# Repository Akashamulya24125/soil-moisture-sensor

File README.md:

\# Soil Moisture Sensor — V1

\### Custom PCB Design · Capacitive Sensing · KiCad · Circuit Simulation

A custom soil-moisture sensing hardware project focused on PCB-level capacitive sensing, analog signal conditioning, circuit simulation, and hardware-to-software interface design.

This repository preserves the \*\*Soil Sensor V1 KiCad design\*\*, supporting design documentation, electrical-rule reports, and PCB fabrication outputs.

\---

\## 1. Project Overview

The objective is to develop a custom soil moisture sensor in which the sensing electrodes are formed directly by copper patterns on the PCB rather than using a separate commercial sensor breakout module.

The probe uses two interlocking copper comb electrodes separated by a small gap. Changes in the surrounding soil environment affect the effective capacitance of the sensing structure. The analog front end converts the resulting electrical response into an output voltage that can be measured by a microcontroller.

The project also defines an interface for reading sensor measurements through an Arduino Uno and displaying moisture readings on a laptop.

\*\*Primary engineering goals\*\*

\- Design the sensor circuitry and PCB using KiCad.

\- Implement a PCB-integrated capacitive sensing structure.

\- Simulate the oscillator and analog signal-conditioning stages.

\- Define a consistent electrical and serial communication interface.

\- Generate fabrication data and document the design for further testing.

\## 2. System Architecture

The documented system follows this signal path:

```text

Soil / Probe Environment

&#x20;         |

&#x20;         v

PCB Capacitive Comb Electrodes

&#x20;         |

&#x20;         v

555-Timer Oscillator

&#x20;         |

&#x20;         v

Sensing Network

&#x20;         |

&#x20;         v

Diode Rectifier + RC Filter

&#x20;         |

&#x20;         v

Analog Output (AOUT)

&#x20;         |

&#x20;         v

Arduino Uno — Analog Input A0

&#x20;         |

&#x20;         v

USB Serial Communication

&#x20;         |

&#x20;         v

Laptop Moisture Monitor Application

```

The custom sensor PCB provides the electrical signal. The Arduino reads the analog output, and the documented serial interface allows the laptop application to display the moisture percentage and raw ADC reading.

This describes the intended system architecture; physical end-to-end validation is still required.

\## 3. Hardware Design

\### PCB-integrated capacitive probe

The sensing element is formed by copper comb patterns in the PCB layout. The electrodes are not separate purchased components.

The soil occupies the electric-field region around and between the fingers. Changes in effective capacitance influence the analog sensing circuit.

Important design considerations include:

\- Electrode geometry and spacing.

\- Protection of the sensing structure from corrosion and unwanted exposure.

\- Separation of the sensing region from the electronics section.

\- Repeatable probe placement during calibration and testing.

\### Analog signal-conditioning circuit

The supplied schematic and circuit-design notes describe a 555-timer oscillator followed by a capacitive sensing network and a diode-based peak detector.

The circuit stages are:

1\. \*\*Oscillator:\*\* Generates the periodic excitation signal.

2\. \*\*Sensing network:\*\* Couples the probe's effective capacitance into the circuit response.

3\. \*\*Rectifier:\*\* Uses a small-signal diode to produce charging pulses.

4\. \*\*Filter and bleed network:\*\* Smooths the rectified signal into an analog output.

5\. \*\*Output interface:\*\* Provides VCC, GND, and AOUT connections.

The exact component packages and values should be checked against the current KiCad project and its committed BOM/footprint revision document.

\## 4. Electrical Interface

The accompanying Interface Control Document defines the intended Arduino-facing interface.

| Signal | Function |

|---|---|

| VCC | Sensor power input |

| GND | Common electrical reference |

| AOUT | Analog sensor output to Arduino A0 |

The documented prototype uses the Arduino Uno's 5 V supply and a common ground. The Arduino's 10-bit ADC produces raw readings in the range 0–1023.

The interface document gives an approximate AOUT expectation of \*\*1.5 V in wet conditions to 3.0 V in dry conditions\*\*. These are design expectations, not confirmed physical measurements.

\## 5. Circuit Simulation and Verification

The supplied simulation report documents electrical-only verification using \*\*KiCad 10 and ngspice\*\*.

\### Simulation configuration

| Parameter | Simulated setting |

|---|---|

| Supply voltage | 5 V DC |

| R1 | 1 kΩ |

| R2 | 10 kΩ |

| C1 | 1 nF |

| R3 | 10 kΩ |

| R4 | 100 kΩ |

| C3 | 10 nF |

| C4 | 100 nF |

| Probe representation | Ideal behavioral capacitance, C5 |

| Capacitance sweep | 100 pF–2.5 nF |

| Transient simulation end time | 50 ms |

\### Observed simulation results

The report records the following simulated behavior:

\- The 555 oscillator produced a repeating waveform at approximately 68.5 kHz.

\- The timing node exhibited the expected charge/discharge behavior.

\- Changes in the modeled sensing capacitance affected the Node-X waveform.

\- The diode exhibited repeated conduction events.

\- The RC network produced a smoother DC output at AOUT.

\- Increasing the modeled capacitance from 100 pF to 2.5 nF reduced the settled simulated AOUT voltage from approximately 2.90 V to 1.52 V.

These results demonstrate the expected behavior of the modeled signal chain under the tested simulation conditions.

\*\*Important distinction:\*\* C5 was an ideal simulated capacitor used to represent the sensing structure. It was not a measured capacitance of the physical PCB probe.

The simulated results therefore do not establish final moisture accuracy, real-soil performance, or the physical probe's dry/wet calibration.

\## 6. Arduino and Laptop Interface

The supplied firmware and application specifications define a wired monitoring architecture.

\### Arduino firmware interface

The firmware specification defines:

\- Analog input: Arduino A0.

\- ADC range: 0–1023.

\- Serial baud rate: 9600.

\- Update interval: 1000 ms, or one reading per second.

\- Output format:

```text

MOISTURE,<percent>,<raw>

```

Example:

```text

MOISTURE,62,743

```

The percentage is constrained to 0–100, while the raw field represents the direct ADC reading.

\### Laptop monitor application

The documented Python GUI is designed to:

\- Discover available serial/COM ports.

\- Connect to the Arduino.

\- Display the latest moisture percentage and raw ADC value.

\- Read serial data in a background thread so the GUI remains responsive.

\- Ignore malformed input lines.

\- Display a no-data status when valid readings have not arrived for more than three seconds.

The companion documents specify this integration contract. Executable firmware and laptop application source files are not included in the current tracked repository snapshot.

\## 7. Calibration and Physical Validation

Calibration values must be measured on the assembled sensor rather than inferred from simulation.

The supplied firmware document lists `DRY\_RAW = 750` and `WET\_RAW = 300` as \*\*placeholders\*\*. They must be replaced with actual measured values before final calibration.

The documented validation sequence is:

1\. Inspect the fabricated PCB and check continuity.

2\. Verify the supply and ground connections before connecting AOUT to the Arduino.

3\. Measure the output with the probe in open air under a controlled dry condition.

4\. Measure the output in the defined wet reference condition.

5\. Record the corresponding raw ADC readings.

6\. Update the firmware calibration constants using those measurements.

7\. Test the complete sensor → Arduino → USB serial → laptop application path.

8\. Evaluate repeatability under controlled soil conditions.

The supplied simulation report explicitly leaves physical probe validation and final dry/wet calibration pending.

\## 8. Repository Contents

The V1 repository contains the following project artifacts:

| File or directory | Purpose |

|---|---|

| `Soil\_Sensor\_v1.kicad\_pro` | KiCad project configuration |

| `Soil\_Sensor\_v1.kicad\_sch` | Circuit schematic |

| `Soil\_Sensor\_v1.kicad\_pcb` | PCB layout |

| `Soil\_Sensor\_v1.csv` | Project CSV data |

| `Soil\_Sensor\_SMD\_BOM\_Footprint\_Revision\_v1.2.pdf` | BOM and footprint revision documentation |

| `DRC.rpt` | Design Rules Checker report |

| `ERC.rpt` | Electrical Rules Checker report |

| `board2pdf.config.ini` | Board-to-PDF configuration |

| `plots/` | Gerber files, drill data, assembly PDF, and simulation-related files |

| `.gitignore` | Excludes selected local and temporary files |

The reports are included for review; their presence alone does not imply that every design rule or electrical check passed.

\## 9. Tools and Technologies

\- \*\*KiCad 10\*\* — schematic capture and PCB design.

\- \*\*ngspice\*\* — electrical circuit simulation.

\- \*\*Arduino Uno\*\* — intended analog measurement and serial interface.

\- \*\*Python / Tkinter / pySerial\*\* — documented laptop-monitor architecture.

\- \*\*Git and GitHub\*\* — version control and preservation of design history.

\## 10. Current Project Status

The V1 KiCad project and its documented fabrication outputs have been committed to Git and uploaded to GitHub.

The supplied simulation report records successful simulation checks of oscillator operation, capacitance-dependent response, rectification, and output smoothing.

The following are not established by those simulation results:

\- Final physical sensor calibration.

\- Accuracy across different soil types.

\- Repeatability of real-world measurements.

\- Final moisture-percentage performance of the assembled system.

These remain hardware-validation tasks rather than assumed achievements.

\## 11. Future Development

Future revisions can build upon the V1 design through documented, traceable changes to the schematic, PCB, sensing geometry, analog front end, calibration process, and system integration.

Each revision should preserve its design files and record its important changes so that previous versions remain available for comparison.

\---

\*\*Project:\*\* Soil Moisture Sensor — V1  

\*\*Design environment:\*\* KiCad 10  

\*\*Simulation environment:\*\* KiCad 10 + ngspice  

\*\*Repository purpose:\*\* Hardware design, documentation, simulation records, and fabrication data

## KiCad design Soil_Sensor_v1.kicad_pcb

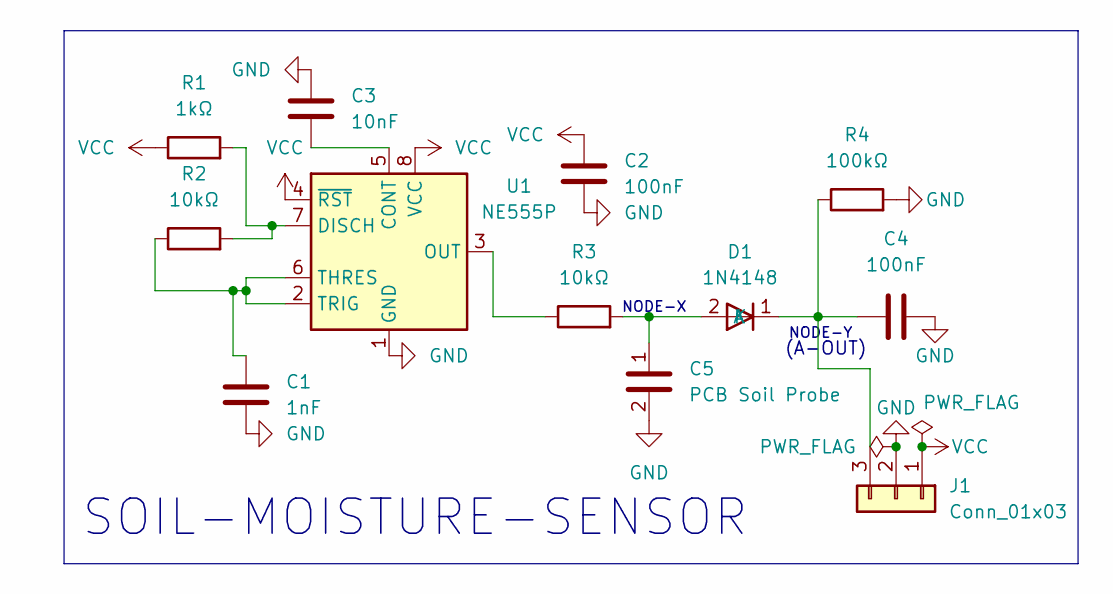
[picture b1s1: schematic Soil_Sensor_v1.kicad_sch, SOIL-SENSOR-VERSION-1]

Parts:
C1: 1nF; C_0805_2012Metric
C2, C4: 100nF; C_0805_2012Metric
C3: 10nF; C_0805_2012Metric
C5: PCB Soil Probe
D1: 1N4148; D_SOD-123
J1: Conn_01x03; PinHeader_1x03_P2.54mm_Vertical
R1: 1kΩ; R_0805_2012Metric
R2, R3: 10kΩ; R_0805_2012Metric
R4: 100kΩ; R_0805_2012Metric
U1: NE555P; DIP-8_W7.62mm

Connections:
GND: C1.2, C2.2, C3.1, C4.2, C5.2, J1.2, R4.2, U1.1 (GND)
unnamed: C5.1, D1.2 (A), R3.2
unnamed: C4.1, D1.1 (K), J1.3, R4.1
unnamed: C3.2, U1.5 (CONT)
unnamed: R1.2, R2.2, U1.7 (DISCH)
unnamed: R3.1, U1.3 (OUT)
unnamed: C1.1, R2.1, U1.2 (TRIG), U1.6 (THRES)
VCC: C2.1, J1.1, R1.1, U1.4 (~RST), U1.8 (VCC)

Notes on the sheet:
NODE-X
NODE-Y
(A-OUT)
SOIL-MOISTURE-SENSOR

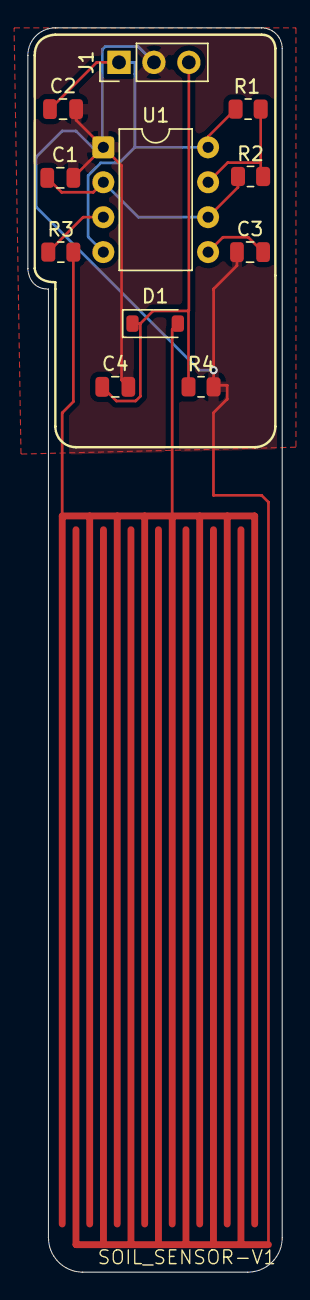
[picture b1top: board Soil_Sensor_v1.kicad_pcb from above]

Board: 2 copper layers, 18.5 x 90.5 mm, 11 parts (0 on the bottom side), 8 nets.
